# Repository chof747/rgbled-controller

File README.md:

# RGB-Led Controller

## Idea

This is a WiFi enabled RGB LED controller with the following features:

- Power in from the main 5V power source and stepping down to 3v3 for the MCU
- Pass through of the power to the led strips
- ESP8266 MCU with boot strap, reset and flash logic
- Programming header for auto-reset and flash enabled programming
- Boot and reset button
- IDC header breaking out I2C, 3v3, GND, FLASH (as additional GPIO) and RESET pin
- LED data out (at level of 5V via level shifter)
- Breakout of not used GPIOs 12-14 plus GND
- Wake up circuit prepared with a solder bridge

The WiFi controller is also ammended by a peripheral board that contains:

- 5 Light and 1 Mod Button
- A Temperature and Humidity Sensor
- An MCP23017 for IO expansion
- A breakout for the unused pins of the IO Expander
- An IDC connection with the same pin-out as the IDC connection of the Controller

## Components

- ESP8266 as an ESP12-F module
- ME6211C33M5G-N (voltage regulator)
- 2n7002 MOSFET (level shifting)
- UMH3N (auto reset circuit)
- Screw terminals for Power in and LED Power + Control out
- IDC 2x3 for I2C breakout
- Std Pin headers for programming header and unused pins breakout
- 0.5A Fuse
- SMD Push buttons
- MCP23017 (I2C)
- SHT40x (temperature controller)
- BAT54C (OR Gate type diodes)

## Revision History

**V1.0** - send to production 26.07.2025

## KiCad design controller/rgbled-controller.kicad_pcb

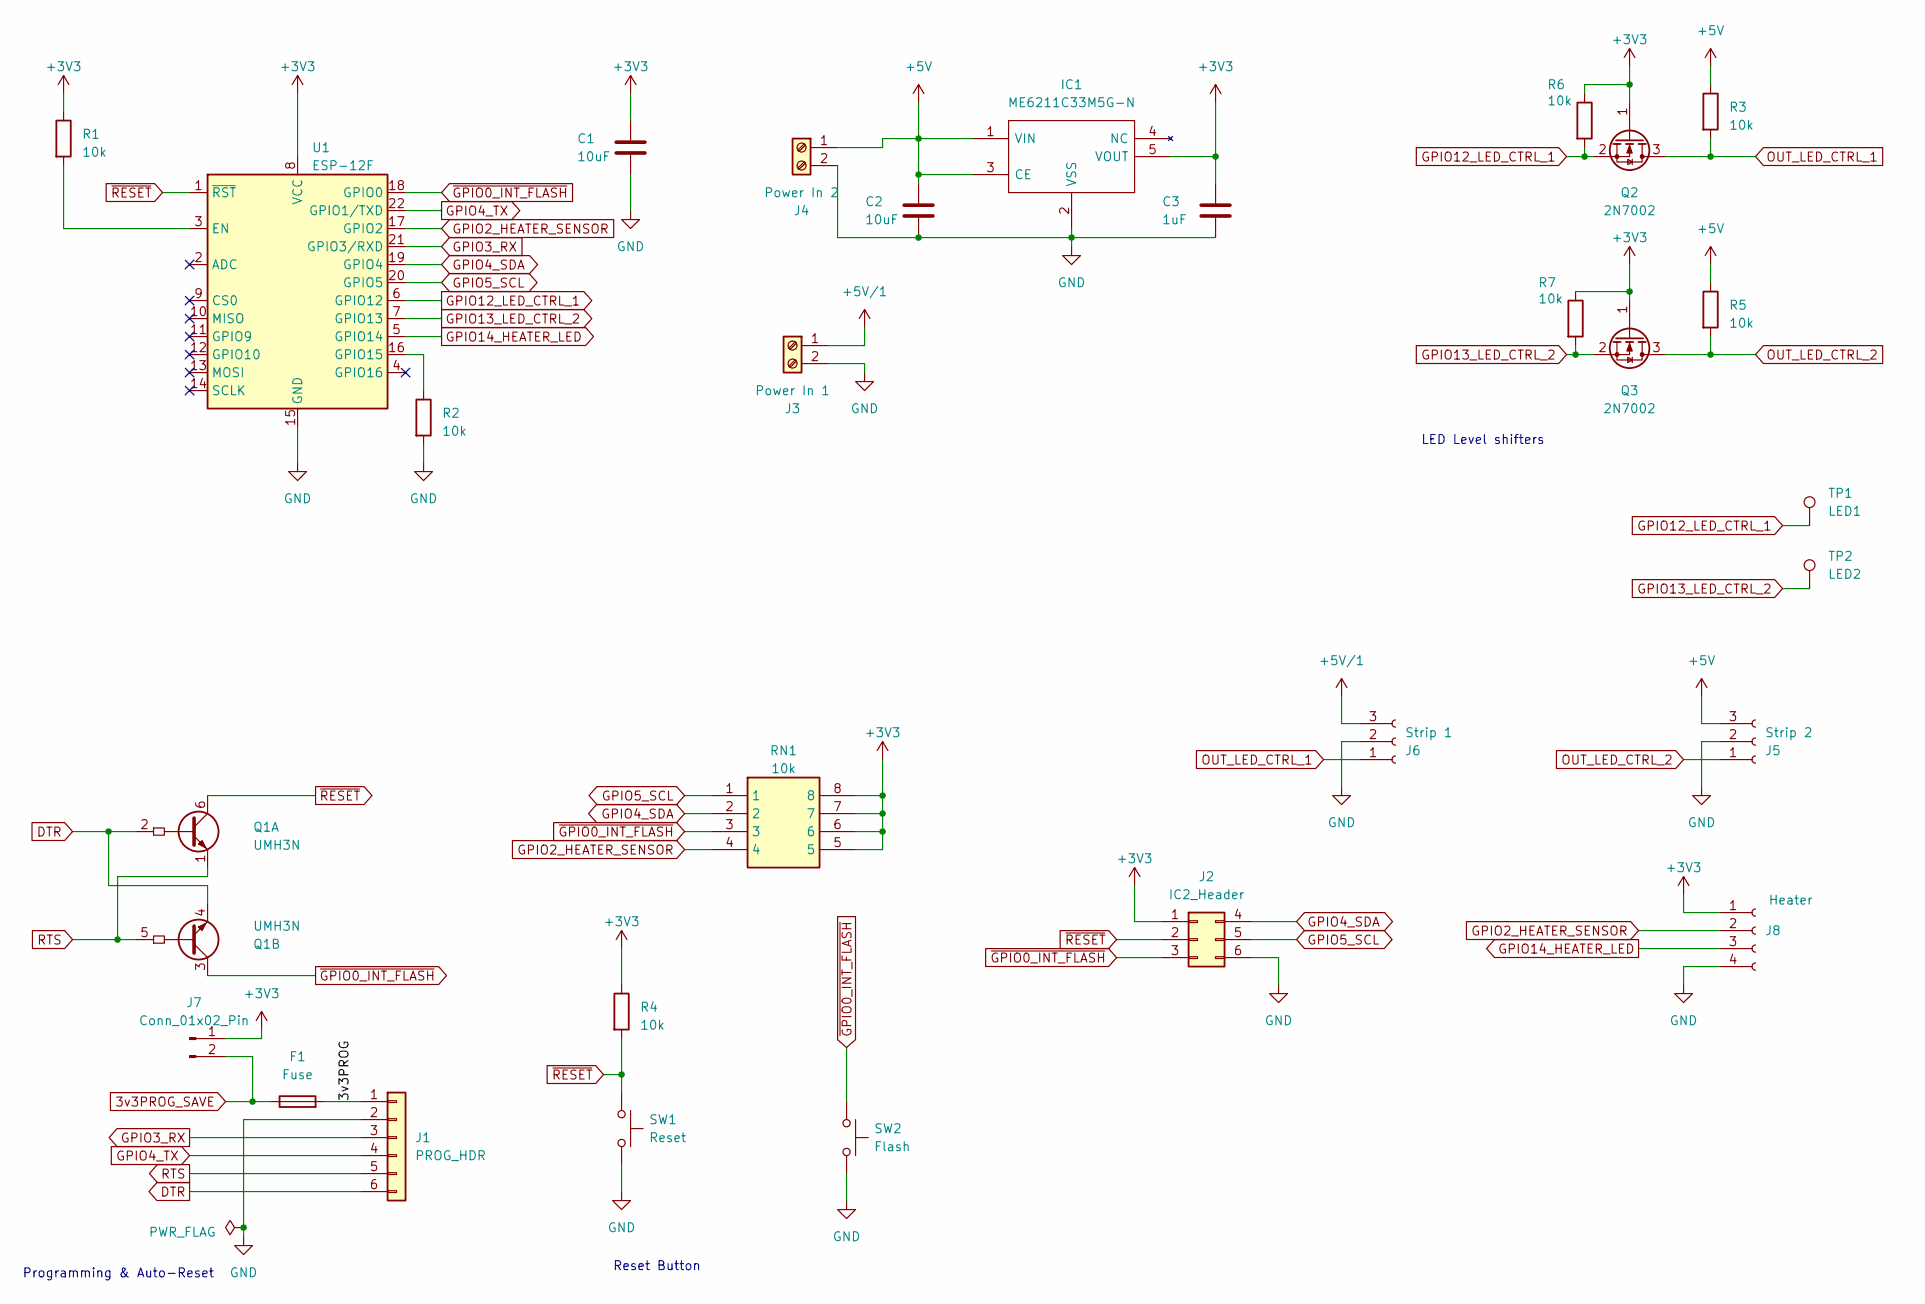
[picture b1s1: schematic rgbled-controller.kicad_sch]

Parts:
C1, C2: 10uF; C_0603_1608Metric_Pad1.08x0.95mm_HandSolder
C3: 1uF; C_0603_1608Metric_Pad1.08x0.95mm_HandSolder
F1: Fuse; Fuse_0805_2012Metric_Pad1.15x1.40mm_HandSolder
IC1: ME6211C33M5G-N; SOT95P270X145-5N; Manufacturer_Part_Number ME6211C33M5G-N
J1: PROG_HDR; PinHeader_1x06_P2.54mm_Vertical
J2: IC2_Header; HDR-TH_6P-P2.54-V-F-R2-C3-S2.54-4
J3: Power In 1; TerminalBlock_bornier-2_P5.08mm
J4: Power In 2; TerminalBlock_bornier-2_P5.08mm
J5: Strip 2; TerminalBlock_bornier-3_P5.08mm
J6: Strip 1; TerminalBlock_bornier-3_P5.08mm
J7: Conn_01x02_Pin; PinHeader_1x02_P2.54mm_Vertical
J8: Heater; CONN-TH_4P-P2.54_KF128-2.54-4P
Q1: UMH3N; SOT-363_SC-70-6
Q2, Q3: 2N7002; SOT-23
R1, R2, R3, R4, R5, R6, R7: 10k; R_0603_1608Metric_Pad0.98x0.95mm_HandSolder
RN1: 10k; YC164JR07220RL; Manufacturer_Part_Number YC164-FR-0710KL; Mouser Part Number 603-YC164-FR-0710KL
SW1: Reset; KEY-SMD_L3.9-W3.0-LS5.0-EH
SW2: Flash; KEY-SMD_L3.9-W3.0-LS5.0-EH
TP1: LED1; TestPoint_Pad_2.0x2.0mm
TP2: LED2; TestPoint_Pad_2.0x2.0mm
U1: ESP-12F; ESP-12E

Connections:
3v3PROG_SAVE: F1.1, J7.2
+3V3: C1.1, C3.1, IC1.5 (VOUT), J2.1, J7.1, J8.1, Q2.1 (G), Q3.1 (G), R1.1, R4.1, R6.1, R7.1, RN1.5, RN1.6, RN1.7, RN1.8, U1.8 (VCC)
+5V: C2.1, IC1.1 (VIN), IC1.3 (CE), J4.1, J5.3, R3.1, R5.1
+5V/1: J3.1, J6.3
/3v3PROG: F1.2, J1.1
DTR: J1.6, Q1.2 (B1), Q1.4 (E2)
GND: C1.2, C2.2, C3.2, IC1.2 (VSS), J1.2, J2.6, J3.2, J4.2, J5.2, J6.2, J8.4, R2.2, SW1.2, SW2.2, U1.15 (GND)
GPIO2_HEATER_SENSOR: J8.2, RN1.4, U1.17 (GPIO2)
GPIO3_RX: J1.3, U1.21 (GPIO3/RXD)
GPIO4_SDA: J2.4, RN1.2, U1.19 (GPIO4)
GPIO4_TX: J1.4, U1.22 (GPIO1/TXD)
GPIO5_SCL: J2.5, RN1.1, U1.20 (GPIO5)
GPIO12_LED_CTRL_1: Q2.2 (S), R6.2, TP1.1, U1.6 (GPIO12)
GPIO13_LED_CTRL_2: Q3.2 (S), R7.2, TP2.1, U1.7 (GPIO13)
GPIO14_HEATER_LED: J8.3, U1.5 (GPIO14)
unnamed: R1.2, U1.3 (EN)
unnamed: R2.1, U1.16 (GPIO15)
OUT_LED_CTRL_1: J6.1, Q2.3 (D), R3.2
OUT_LED_CTRL_2: J5.1, Q3.3 (D), R5.2
RTS: J1.5, Q1.1 (E1), Q1.5 (B2)
~GPIO0_INT_FLASH: J2.3, Q1.3 (C2), RN1.3, SW2.1, U1.18 (GPIO0)
~RESET: J2.2, Q1.6 (C1), R4.2, SW1.1, U1.1 (~RST)

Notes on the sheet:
Programming & Auto-Reset
Reset Button
LED Level shifters

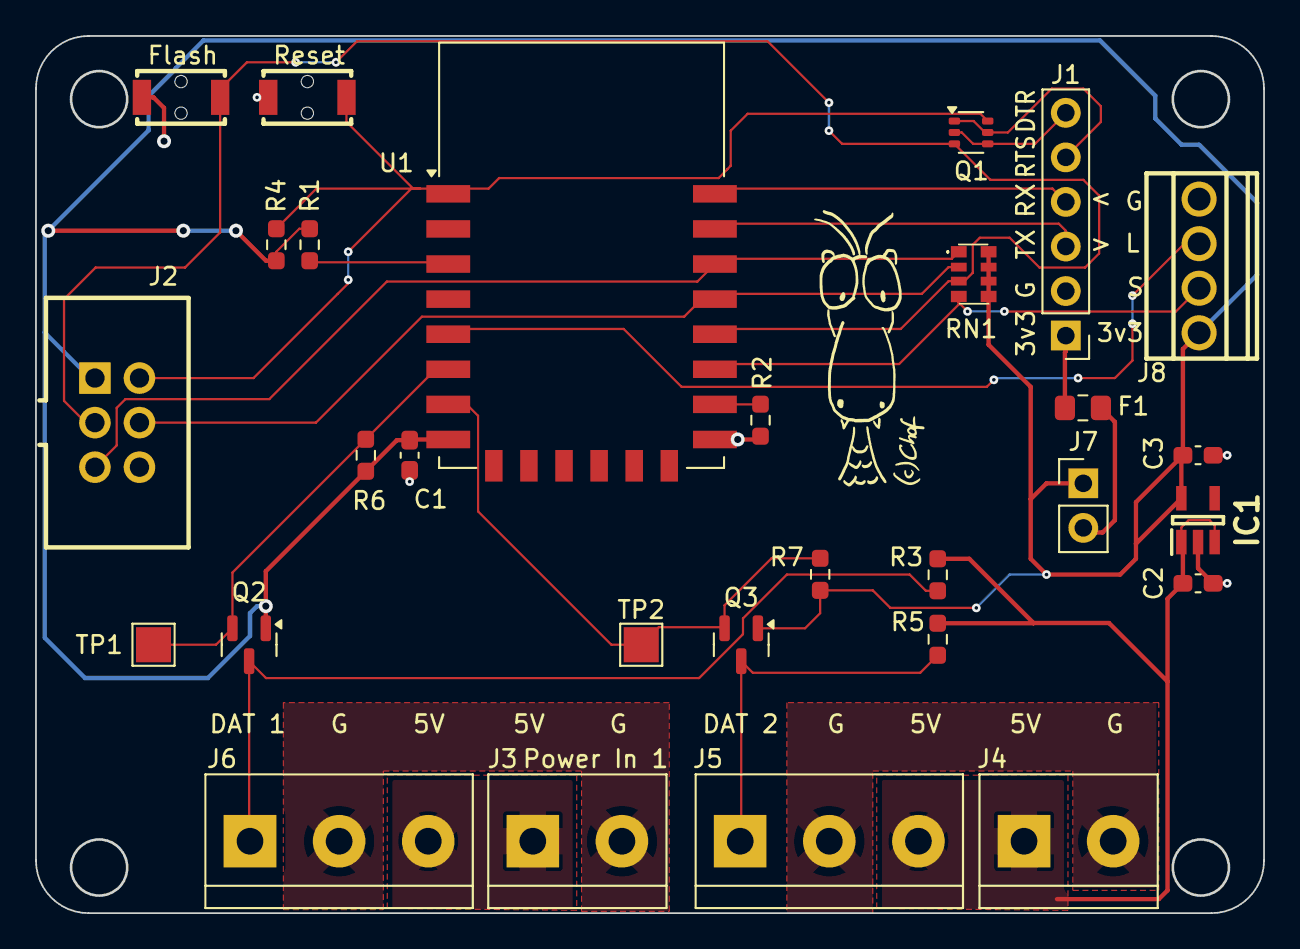
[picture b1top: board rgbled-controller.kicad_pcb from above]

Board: 2 copper layers, 70.0 x 49.9 mm, 29 parts (0 on the bottom side), 22 nets.

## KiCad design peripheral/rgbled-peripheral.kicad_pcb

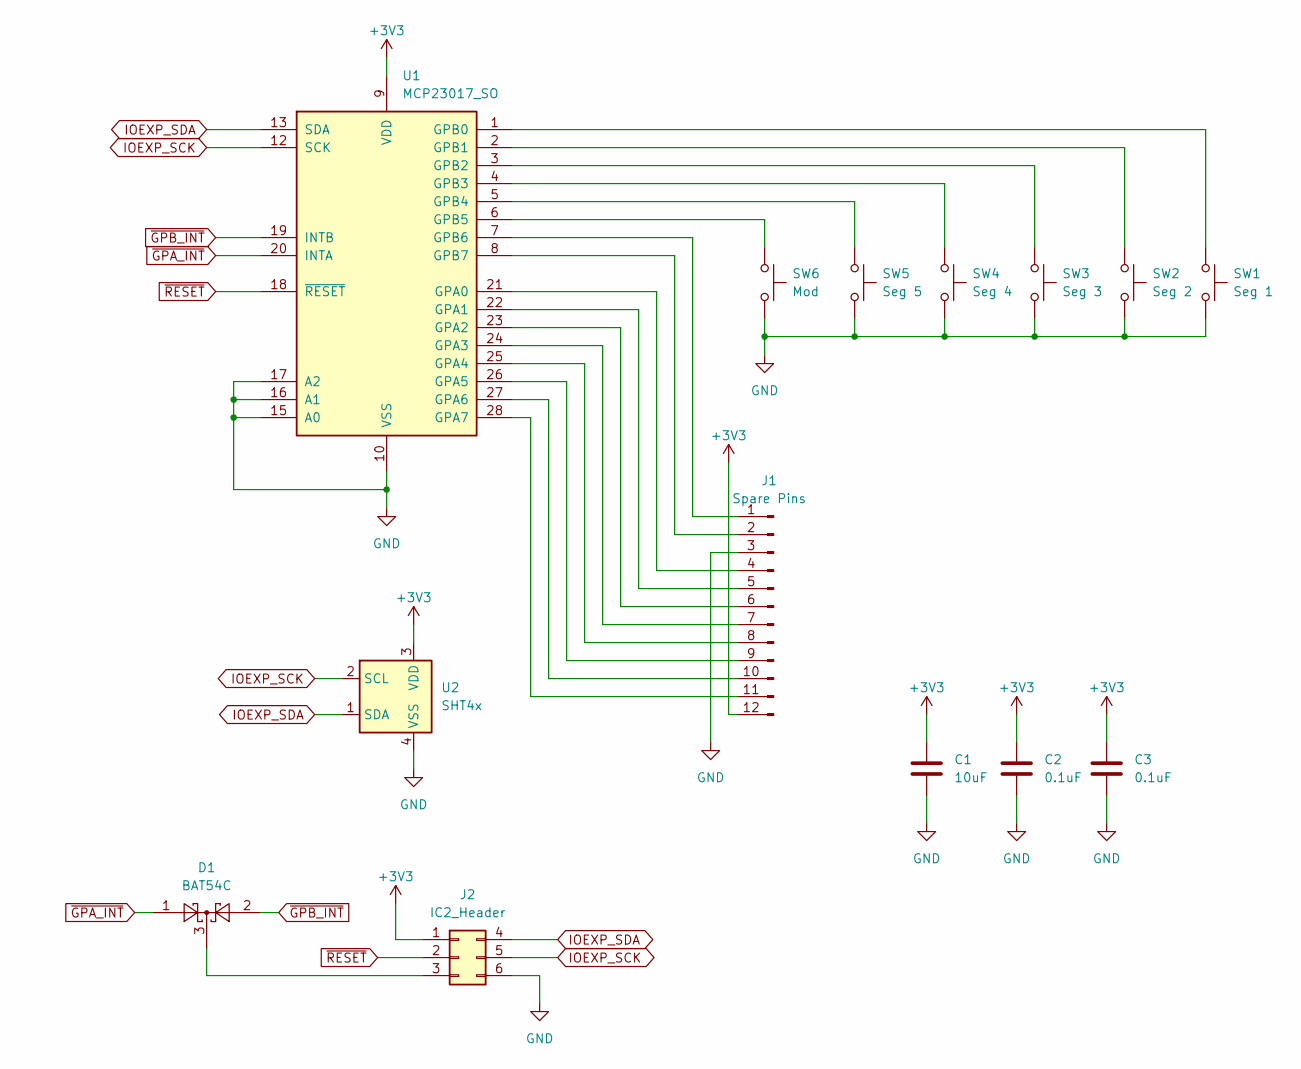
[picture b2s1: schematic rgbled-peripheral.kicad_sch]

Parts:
C1: 10uF; C_0603_1608Metric_Pad1.08x0.95mm_HandSolder
C2, C3: 0.1uF; C_0603_1608Metric_Pad1.08x0.95mm_HandSolder
D1: BAT54C; SOT-23
J1: Spare Pins; PinHeader_1x12_P2.54mm_Vertical
J2: IC2_Header; HDR-TH_6P-P2.54-V-F-R2-C3-S2.54-4
SW1: Seg 1; KEY-SMD_L3.9-W3.0-LS5.0-EH
SW2: Seg 2; KEY-SMD_L3.9-W3.0-LS5.0-EH
SW3: Seg 3; KEY-SMD_L3.9-W3.0-LS5.0-EH
SW4: Seg 4; KEY-SMD_L3.9-W3.0-LS5.0-EH
SW5: Seg 5; KEY-SMD_L3.9-W3.0-LS5.0-EH
SW6: Mod; KEY-SMD_L3.9-W3.0-LS5.0-EH
U1: MCP23017_SO; SOIC-28W_7.5x17.9mm_P1.27mm
U2: SHT4x; Sensirion_DFN-4_1.5x1.5mm_P0.8mm_SHT4x_NoCentralPad

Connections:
+3V3: C1.1, C2.1, C3.1, J1.12, J2.1, U1.9 (VDD), U2.3 (VDD)
GND: C1.2, C2.2, C3.2, J1.3, J2.6, SW1.2, SW2.2, SW3.2, SW4.2, SW5.2, SW6.2, U1.10 (VSS), U1.15 (A0), U1.16 (A1), U1.17 (A2), U2.4 (VSS)
IOEXP_SCK: J2.5, U1.12 (SCK), U2.2 (SCL)
IOEXP_SDA: J2.4, U1.13 (SDA), U2.1 (SDA)
unnamed: J1.1, U1.7 (GPB6)
unnamed: J1.2, U1.8 (GPB7)
unnamed: J1.4, U1.21 (GPA0)
unnamed: J1.5, U1.22 (GPA1)
unnamed: J1.6, U1.23 (GPA2)
unnamed: J1.7, U1.24 (GPA3)
unnamed: J1.8, U1.25 (GPA4)
unnamed: J1.9, U1.26 (GPA5)
unnamed: J1.10, U1.27 (GPA6)
unnamed: J1.11, U1.28 (GPA7)
unnamed: D1.3, J2.3
unnamed: SW1.1, U1.1 (GPB0)
unnamed: SW2.1, U1.2 (GPB1)
unnamed: SW3.1, U1.3 (GPB2)
unnamed: SW4.1, U1.4 (GPB3)
unnamed: SW5.1, U1.5 (GPB4)
unnamed: SW6.1, U1.6 (GPB5)
~GPA_INT: D1.1, U1.20 (INTA)
~GPB_INT: D1.2, U1.19 (INTB)
~RESET: J2.2, U1.18 (~RESET)

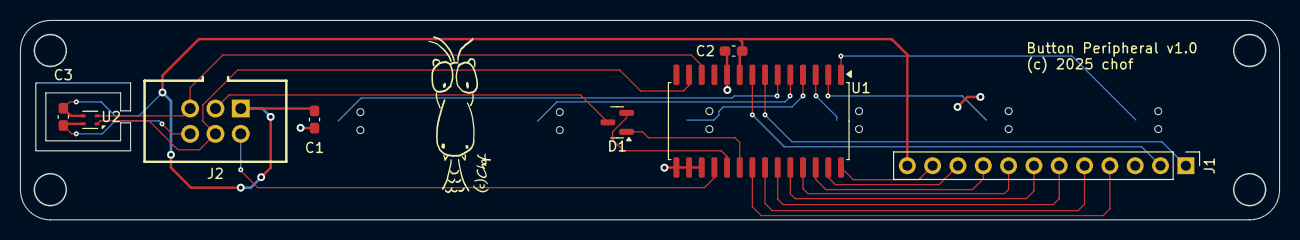
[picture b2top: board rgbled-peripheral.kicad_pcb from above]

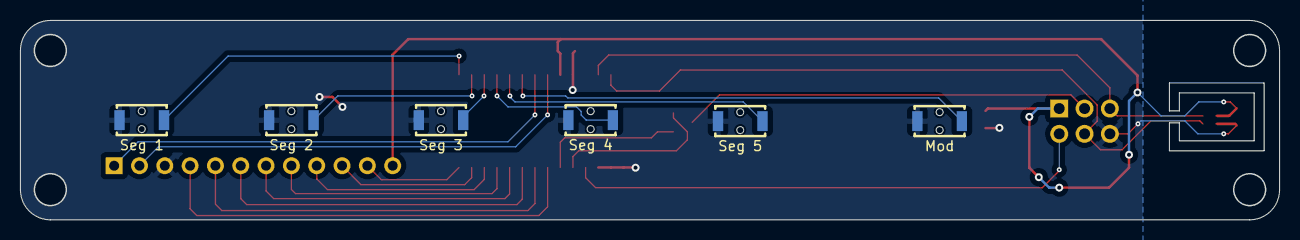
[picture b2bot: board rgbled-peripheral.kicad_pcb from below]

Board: 2 copper layers, 126.3 x 19.9 mm, 14 parts (6 on the bottom side), 24 nets.

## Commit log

2025-06-30 first version of rgbled controller - no crc check done yet
2025-07-01 added 3 mounting points and crc check complete
2025-07-02 changed board layout and added spare pins
2025-07-02 Added README
2025-07-16 Finalized first version of controller board and moved it into controller subdirectory
2025-07-18 added peripheral board and updated README
2025-07-26 initial production version
2025-07-26 Readme updates

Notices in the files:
controller/rgbled-controller.kicad_pcb:
chof (c)2025
peripheral/rgbled-peripheral.kicad_pcb:
(c) 2025 chof
